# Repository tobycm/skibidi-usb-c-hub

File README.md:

# Skibidi USB C Hub

speedrunning a usb a to 4 port usb c hub in school xd

i had an old computer that only has usb a ports, so i made this hub to extend those ports to usb c

ch334 my love. i <3 wch

## Links

Onshape: https://cad.onshape.com/documents/2453a6f2426758a8164db13e/w/aaae3aa11a76b09d86b06c41/e/a0f10c7f22eb2d735bb89467?renderMode=0&uiState=698d8565a52609b0fe224337

Kicanvas: https://kicanvas.org/?repo=https%3A%2F%2Fgithub.com%2Ftobycm%2Fskibidi-usb-c-hub%2Ftree%2Fmain%2Fpcb

Repo: https://github.com/tobycm/skibidi-usb-c-hub

## 3D render

## PCB

## BOM

| Description | Quantity | Part # | Unit Price | Extended Price USD | Product Link |
| :--- | :---: | :--- | :---: | :---: | :--- |
| USB-A (USB TYPE-A) Receptacle Connector 4 Position Right Angle | 20 | AM90 | 0.0646 | 1.29 | [Link](https://www.lcsc.com/product-detail/C404965.html) |
| Polymeric PTC Resettable Fuse 12V 2A Surface Mount 1206 | 20 | BSMD1206-200-12V | 0.0612 | 1.22 | [Link](https://www.lcsc.com/product-detail/C883135.html) |
| 18.6VC Clamp 9.4A@8/20us Ipp ESD DIODE SOD-523 | 20 | ESD5Z5.0T1G | 0.0387 | 0.77 | [Link](https://www.lcsc.com/product-detail/C82044.html) |
| 220Ω@100MHz 1 Line Ferrite Bead 0805 2A 45mΩ | 50 | BLM21PG221SN1D | 0.0167 | 0.84 | [Link](https://www.lcsc.com/product-detail/C85840.html) |
| 220uF ±20% 10V SMD,D6.3xL5.8mm 2000hrs | 20 | HV1A227M0605PZ | 0.1242 | 2.48 | [Link](https://www.lcsc.com/product-detail/C5246513.html) |
| LCSC Shipping | - | LCSC Shipping | 13.16 | 13.16 | [Link](https://www.lcsc.com/) |
| LCSC Handling Fee | - | LCSC Handling Fee | 3 | 3 | [Link](https://www.lcsc.com/) |
| PCB | - | PCB | 6.1 | 6.1 | [Link](https://jlcpcb.com/) |
| PCBA | - | PCBA | 25.44 | 25.44 | [Link](https://jlcpcb.com/) |
| JLCPCB Shipping | - | JLCPCB Shipping | 8.53 | 8.53 | [Link](https://jlcpcb.com/) |
| **Total** | | | | **62.84** | |

## End notes

This project was funded by [Blueprint](https://blueprint.hackclub.com/), a grant program by Hack Club that supports open source hardware projects for teenagers.

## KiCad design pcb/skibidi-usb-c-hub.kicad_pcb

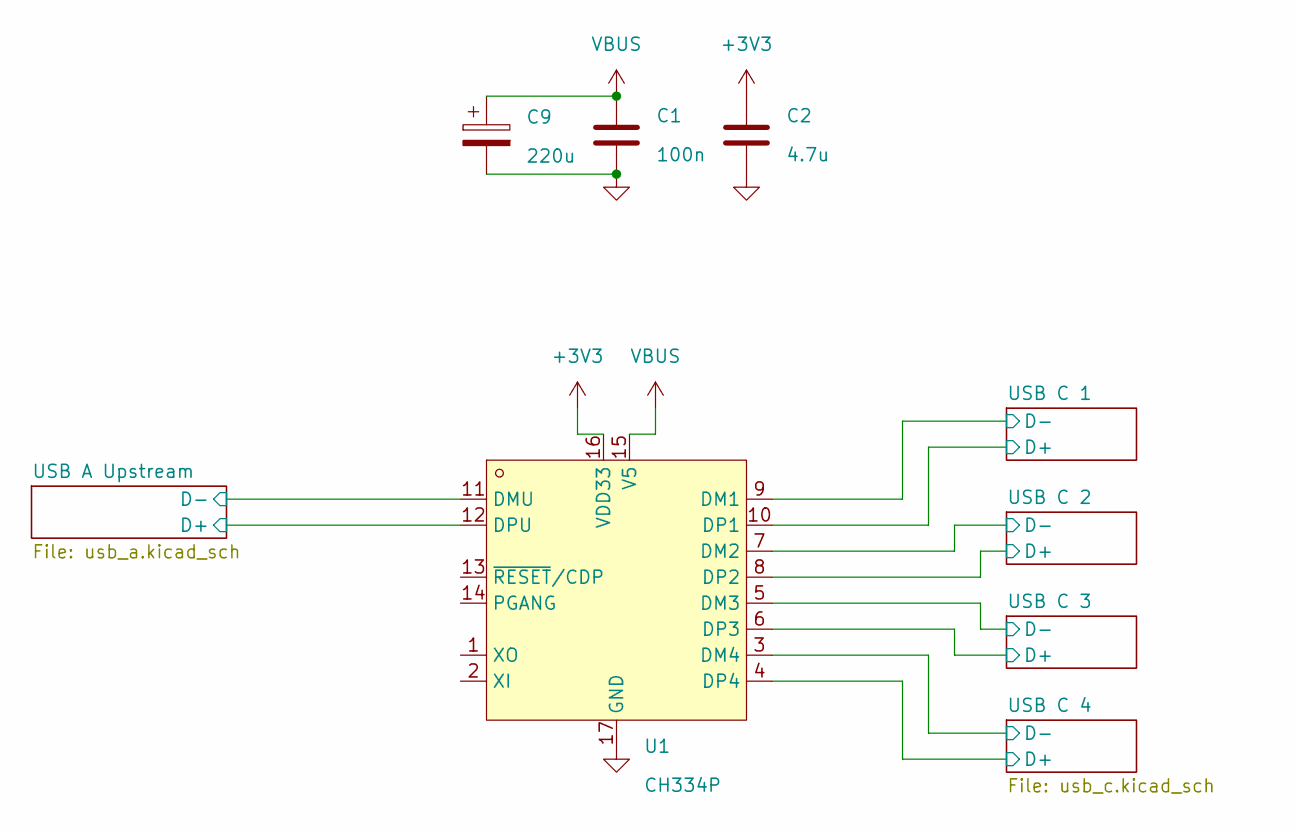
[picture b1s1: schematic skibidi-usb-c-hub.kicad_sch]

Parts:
C1: 100n; C_0402_1005Metric; LCSC Part # C1525
C2: 4.7u; C_0402_1005Metric; LCSC Part # C23733
C9: 220u; CP_Elec_6.3x5.8; LCSC Part # C5246513
U1: CH334P; QFN-16_L3.0-W3.0-P0.50-BL-EP1.7; LCSC Part C5373042

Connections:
+3V3: C2.1, U1.16 (VDD33)
/USB A Upstream/D+: U1.12 (DPU); also elsewhere on the board
/USB A Upstream/D-: U1.11 (DMU); also elsewhere on the board
/USB C 1/D+: U1.10 (DP1); also elsewhere on the board
/USB C 1/D-: U1.9 (DM1); also elsewhere on the board
/USB C 2/D+: U1.8 (DP2); also elsewhere on the board
/USB C 2/D-: U1.7 (DM2); also elsewhere on the board
/USB C 3/D+: U1.6 (DP3); also elsewhere on the board
/USB C 3/D-: U1.5 (DM3); also elsewhere on the board
/USB C 4/D+: U1.4 (DP4); also elsewhere on the board
/USB C 4/D-: U1.3 (DM4); also elsewhere on the board
GND: C1.2, C2.2, C9.2, U1.17 (GND); also elsewhere on the board
VBUS: C1.1, C9.1, U1.15 (V5); also elsewhere on the board

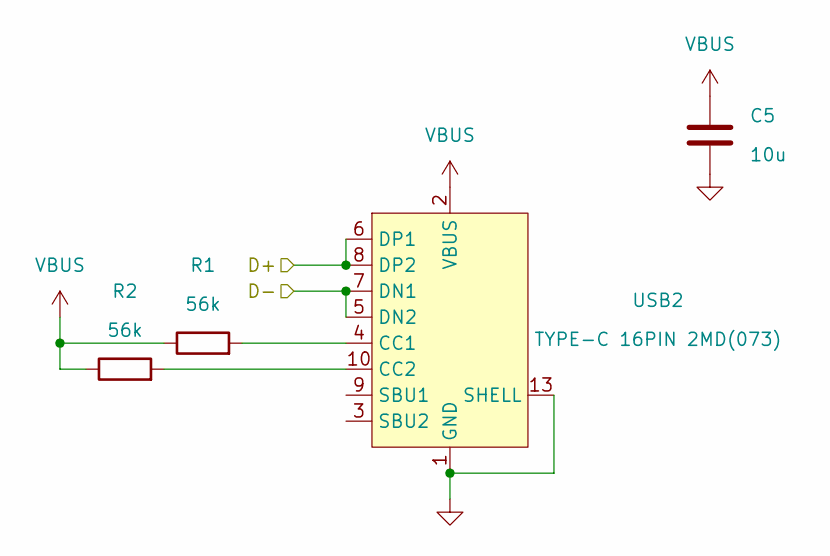
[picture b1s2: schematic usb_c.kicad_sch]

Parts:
C5: 10u; C_0603_1608Metric; LCSC Part # C96446
R1, R2: 56k; R_0603_1608Metric; LCSC Part # C23206
USB2: TYPE-C 16PIN 2MD(073); USB-C-SMD_TYPE-C-6PIN-2MD-073; LCSC Part C2765186

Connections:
/USB C 1/D+: USB2.6 (DP1), USB2.8 (DP2); also elsewhere on the board
/USB C 1/D-: USB2.5 (DN2), USB2.7 (DN1); also elsewhere on the board
GND: C5.2, USB2.1 (GND), USB2.12 (GND), USB2.13 (SHELL), USB2.14 (SHELL); also elsewhere on the board
unnamed: R1.2, USB2.4 (CC1)
unnamed: R2.2, USB2.10 (CC2)
VBUS: C5.1, R1.1, R2.1, USB2.2 (VBUS), USB2.11 (VBUS); also elsewhere on the board

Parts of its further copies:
C6, C7, C8: 10u; C_0603_1608Metric; LCSC Part # C96446
R3, R4, R5, R6, R7, R8: 56k; R_0603_1608Metric; LCSC Part # C23206
USB3, USB4, USB5: TYPE-C 16PIN 2MD(073); USB-C-SMD_TYPE-C-6PIN-2MD-073; LCSC Part C2765186

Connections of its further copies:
/USB C 2/D+: USB3.6 (DP1), USB3.8 (DP2); also elsewhere on the board
/USB C 2/D-: USB3.5 (DN2), USB3.7 (DN1); also elsewhere on the board
/USB C 3/D+: USB4.6 (DP1), USB4.8 (DP2); also elsewhere on the board
/USB C 3/D-: USB4.5 (DN2), USB4.7 (DN1); also elsewhere on the board
/USB C 4/D+: USB5.6 (DP1), USB5.8 (DP2); also elsewhere on the board
/USB C 4/D-: USB5.5 (DN2), USB5.7 (DN1); also elsewhere on the board
GND: C6.2, C7.2, C8.2, USB3.1 (GND), USB3.12 (GND), USB3.13 (SHELL), USB3.14 (SHELL), USB4.1 (GND), USB4.12 (GND), USB4.13 (SHELL), USB4.14 (SHELL), USB5.1 (GND), USB5.12 (GND), USB5.13 (SHELL), USB5.14 (SHELL); also elsewhere on the board
unnamed: R3.2, USB3.4 (CC1)
unnamed: R4.2, USB3.10 (CC2)
unnamed: R5.2, USB4.4 (CC1)
unnamed: R6.2, USB4.10 (CC2)
unnamed: R7.2, USB5.4 (CC1)
unnamed: R8.2, USB5.10 (CC2)
VBUS: C6.1, C7.1, C8.1, R3.1, R4.1, R5.1, R6.1, R7.1, R8.1, USB3.2 (VBUS), USB3.11 (VBUS), USB4.2 (VBUS), USB4.11 (VBUS), USB5.2 (VBUS), USB5.11 (VBUS); also elsewhere on the board

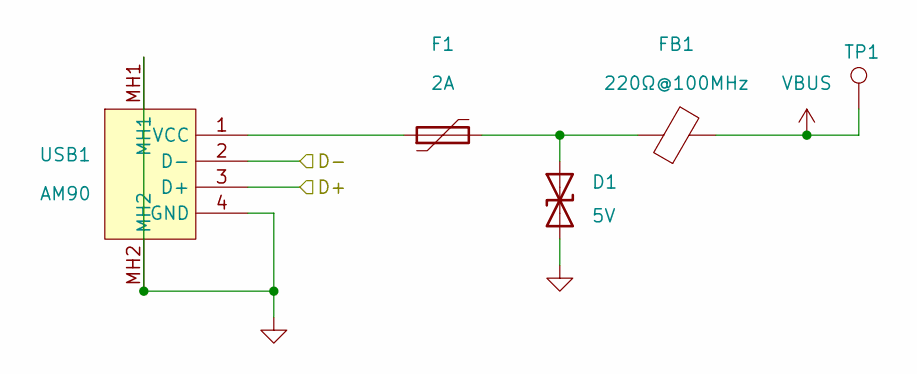
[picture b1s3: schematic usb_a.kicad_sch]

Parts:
D1: 5V; D_SOD-523; LCSC Part # C82044
F1: 2A; Fuse_1206_3216Metric; LCSC Part # C883135
FB1: 220Ω@100MHz; R_0805_2012Metric_Pad1.20x1.40mm_HandSolder; LCSC Part # C85840
TP1: TestPoint; TestPoint_Pad_D2.5mm
USB1: AM90; USB-AM-TH_AM90; LCSC Part C404965

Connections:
/USB A Upstream/D+: USB1.3 (D+); also elsewhere on the board
/USB A Upstream/D-: USB1.2 (D-); also elsewhere on the board
GND: D1.2 (A2), USB1.4 (GND), USB1.MH1, USB1.MH2; also elsewhere on the board
unnamed: D1.1 (A1), F1.2, FB1.1
unnamed: F1.1, USB1.1 (VCC)
VBUS: FB1.2, TP1.1; also elsewhere on the board

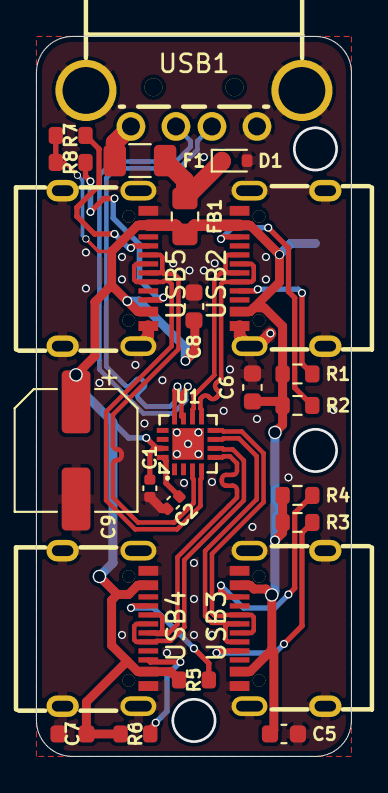
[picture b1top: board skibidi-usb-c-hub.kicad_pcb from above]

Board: 2 copper layers, 17.5 x 40.0 mm, 25 parts (1 on the bottom side), 23 nets.

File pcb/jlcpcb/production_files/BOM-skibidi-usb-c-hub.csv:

Comment,Designator,Footprint,LCSC,Quantity
100n,C1,C_0402_1005Metric,C1525,1
10u,"C5,C6,C7,C8",C_0603_1608Metric,C96446,4
4.7u,C2,C_0402_1005Metric,C23733,1
56k,"R1,R2,R3,R4,R5,R6,R7,R8",R_0603_1608Metric,C23206,8
CH334P,U1,QFN-16_L3.0-W3.0-P0.50-BL-EP1.7,C5373042,1
TYPE-C 16PIN 2MD(073),"USB2,USB3,USB4,USB5",USB-C-SMD_TYPE-C-6PIN-2MD-073,C2765186,4
TestPoint,TP1,TestPoint_Pad_D2.5mm,,1

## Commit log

2026-02-09 init project
2026-02-09 schematic done
2026-02-09 pcb half way done
2026-02-10 finished pcb and bom, added schematic pdf, step file for pcb, and gerbers
2026-02-12 add cad for case
2026-02-23 add bom that got ignored by gitignore :skull:
2026-04-25 add ibom
